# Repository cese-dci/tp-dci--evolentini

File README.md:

# Punku, Control de Accesos

## Diagramas de Hardware

Este repositorio contiene el los diagramas esquematicos y diseño de placas del equipo apra control de accesos Punku. Los mismo estan realizados utilizando la el programa [KiCad](http://kicad.org/)

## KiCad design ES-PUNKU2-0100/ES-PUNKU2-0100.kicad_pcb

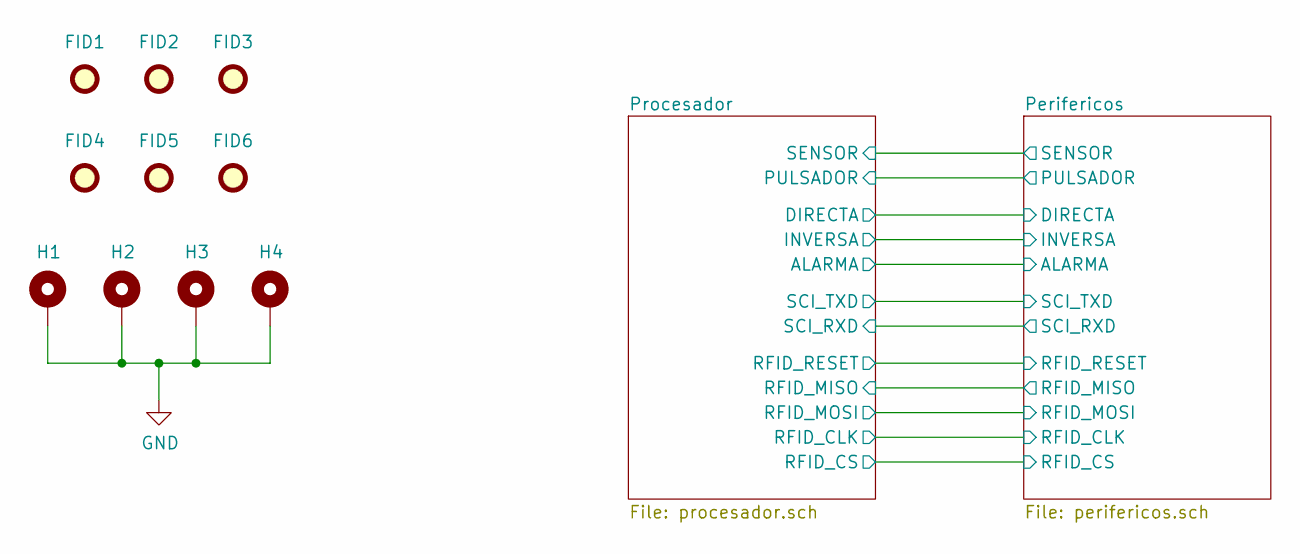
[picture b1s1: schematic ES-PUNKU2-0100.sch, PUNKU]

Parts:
FID1, FID2, FID3, FID4, FID5, FID6: Fiducial; Fiducial_0.5mm_Mask1mm
H1, H2, H3, H4: MountingHole_Pad; MountingHole_4mm_Pad

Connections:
GND: H1.1, H2.1, H3.1, H4.1; also elsewhere on the board

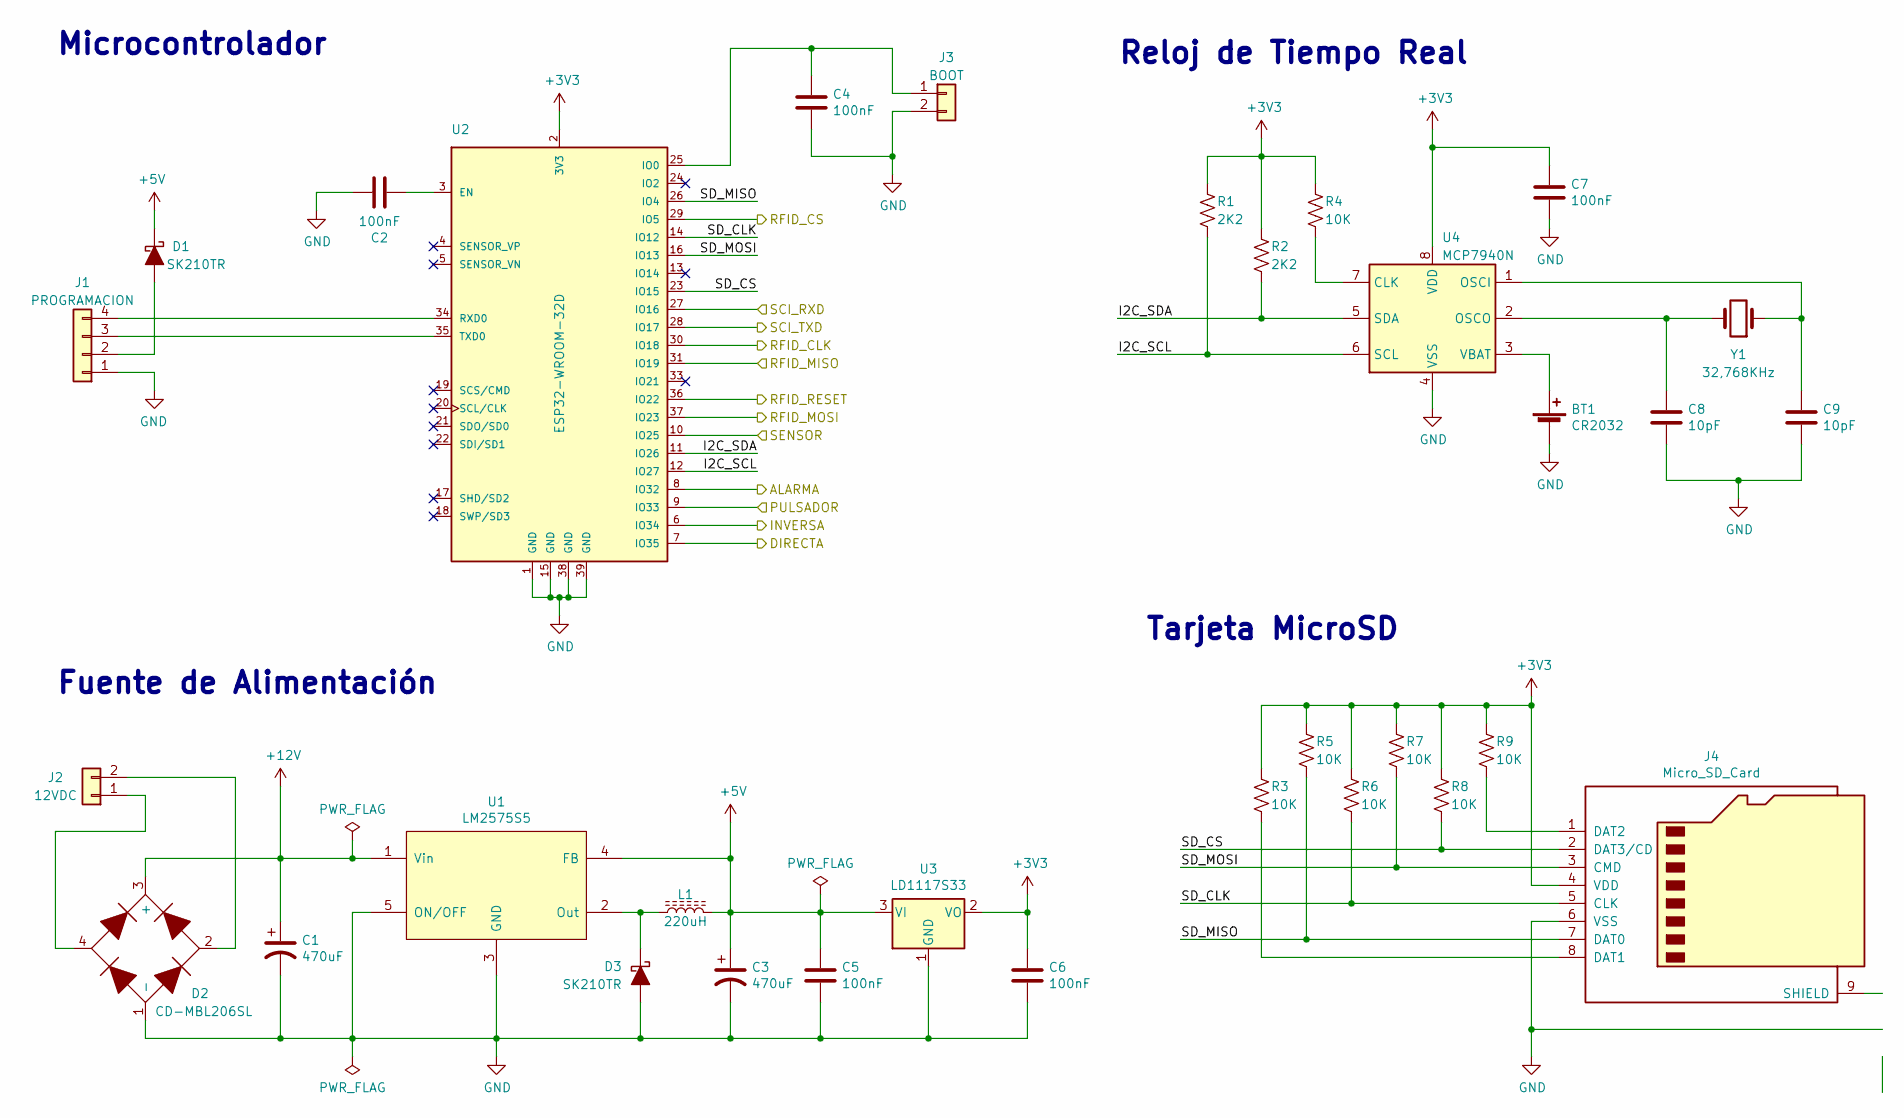
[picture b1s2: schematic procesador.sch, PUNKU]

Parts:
BT1: CR2032; BatteryHolder_Keystone_1058_1x2032; DigiKey 36-1058-ND
C1, C3: 470uF; CP_Elec_8x10
C2, C4, C5, C6, C7: 100nF; C_1206_0805_Dual
C8, C9: 10pF; C_1206_0805_Dual
D1, D3: SK210TR; DO-214AA; DigiKey 1655-1584-1-ND
D2: CD-MBL206SL; BOURNS-0.23x0.20; DigiKey CD-MBL206SLCT-ND
J1: PROGRAMACION; Pin_Header_Straight_1x04_Pitch2.54mm
J2: 12VDC; Bornera_Recta_2_0.200_Inch
J3: BOOT; Pin_Header_Straight_1x02_Pitch2.54mm
J4: Micro_SD_Card; SD_AMPHENOL_114_00841_68; DigiKey 114-00841-68-1-ND
L1: 220uH; BOURNS_INDUCTOR_SRR1260; DigiKey SRR1280-331KLCT-ND
R1, R2: 2K2; R_1206_0805_Dual
R3, R4, R5, R6, R7, R8, R9: 10K; R_1206_0805_Dual
U1: LM2575S5; D2PAK_TO-263_5Patas; DigiKey LM2575S-5.0/NOPB-ND
U2: ESP32-WROOM-32D; MODULE_ESP32-WROOM-32D; DigiKey 1904-1023-1-ND
U3: LD1117S33; SOT-223-3_TabPin2; DigiKey 497-1241-1-ND
U4: MCP7940N; SOIC-8; DigiKey MCP7940NT-I/SNCT-ND
Y1: 32,768KHz; CRISTAL_EPSON_3,2mm_1,5mm; DigiKey SER4089CT-ND

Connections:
+3V3: C6.1, C7.1, J4.4 (VDD), R1.1, R2.1, R3.1, R4.1, R5.1, R6.1, R7.1, R8.1, R9.1, U2.2 (3V3), U3.2 (VO), U4.8 (VDD); also elsewhere on the board
+5V: C3.1, C5.1, D1.1 (K), L1.2, U1.4 (FB), U3.3 (VI); also elsewhere on the board
+12V: C1.1, D2.3 (+), U1.1 (Vin); also elsewhere on the board
/Perifericos/ALARMA: U2.8 (IO32); also elsewhere on the board
/Perifericos/DIRECTA: U2.7 (IO35); also elsewhere on the board
/Perifericos/INVERSA: U2.6 (IO34); also elsewhere on the board
/Perifericos/PULSADOR: U2.9 (IO33); also elsewhere on the board
/Perifericos/RFID_CLK: U2.30 (IO18); also elsewhere on the board
/Perifericos/RFID_CS: U2.29 (IO5); also elsewhere on the board
/Perifericos/RFID_MISO: U2.31 (IO19); also elsewhere on the board
/Perifericos/RFID_MOSI: U2.37 (IO23); also elsewhere on the board
/Perifericos/RFID_RESET: U2.36 (IO22); also elsewhere on the board
/Perifericos/SCI_RXD: U2.27 (IO16); also elsewhere on the board
/Perifericos/SCI_TXD: U2.28 (IO17); also elsewhere on the board
/Perifericos/SENSOR: U2.10 (IO25); also elsewhere on the board
/Procesador/I2C_SCL: R1.2, U2.12 (IO27), U4.6 (SCL)
/Procesador/I2C_SDA: R2.2, U2.11 (IO26), U4.5 (SDA)
/Procesador/SD_CLK: J4.5 (CLK), R6.2, U2.14 (IO12)
/Procesador/SD_CS: J4.2 (DAT3/CD), R8.2, U2.23 (IO15)
/Procesador/SD_MISO: J4.7 (DAT0), R5.2, U2.26 (IO4)
/Procesador/SD_MOSI: J4.3 (CMD), R7.2, U2.16 (IO13)
GND: BT1.2 (-), C1.2, C2.1, C3.2, C4.1, C5.2, C6.2, C7.2, C8.2, C9.2, D2.1 (-), D3.2 (A), J1.1, J3.2, J4.6 (VSS), J4.9 (SHIELD), U1.3 (GND), U1.5 (ON/OFF), U2.1 (GND), U2.15 (GND), U2.38 (GND), U2.39 (GND), U3.1 (GND), U4.4 (VSS); also elsewhere on the board
unnamed: BT1.1 (+), U4.3 (VBAT)
unnamed: C2.2, U2.3 (EN)
unnamed: C4.2, J3.1, U2.25 (IO0)
unnamed: C8.1, U4.2 (OSCO), Y1.2
unnamed: C9.1, U4.1 (OSCI), Y1.1
unnamed: D1.2 (A), J1.2
unnamed: D2.2, J2.2
unnamed: D2.4, J2.1
unnamed: D3.1 (K), L1.1, U1.2 (Out)
unnamed: J1.3, U2.35 (TXD0)
unnamed: J1.4, U2.34 (RXD0)
unnamed: J4.1 (DAT2), R9.2
unnamed: J4.8 (DAT1), R3.2
unnamed: R4.2, U4.7 (CLK)

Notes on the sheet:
Microcontrolador
Tarjeta MicroSD
Reloj de Tiempo Real
Fuente de Alimentación

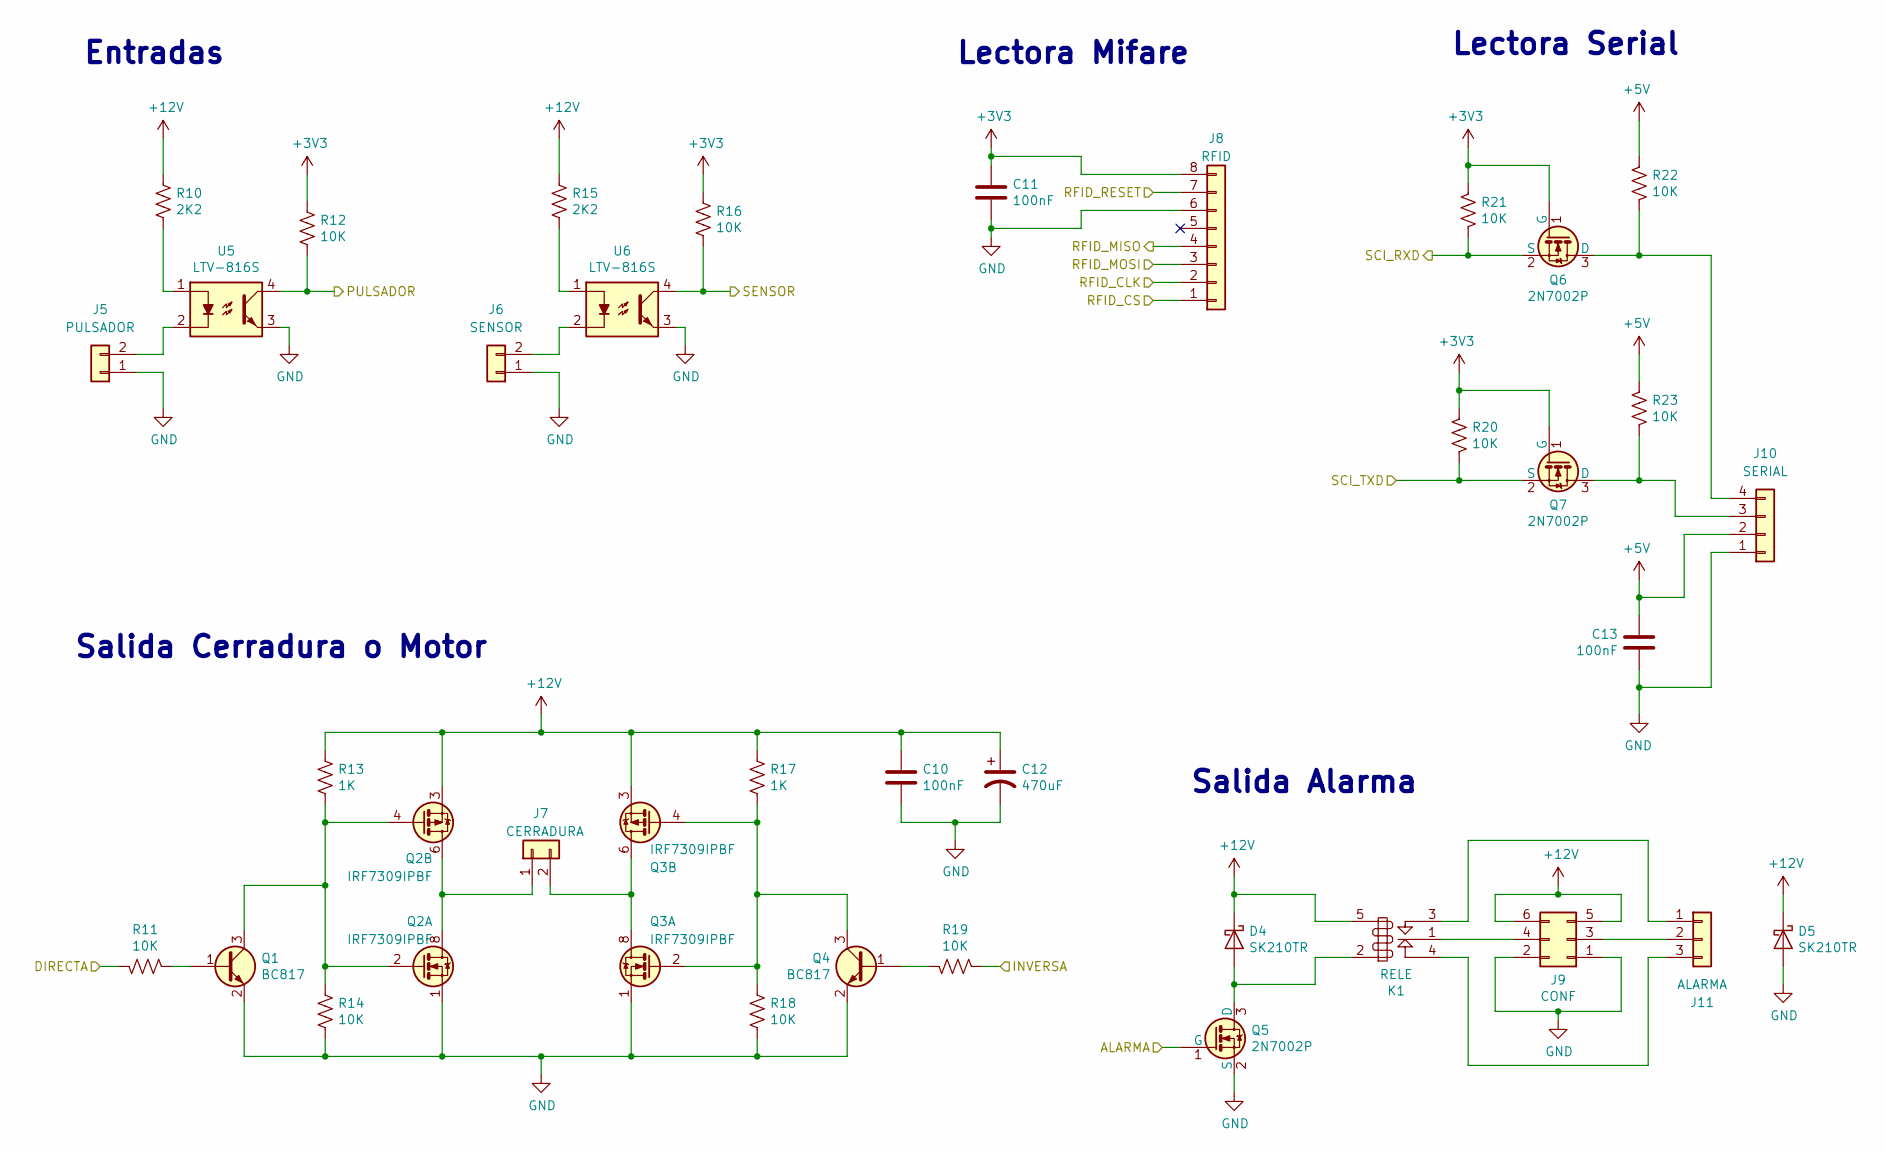
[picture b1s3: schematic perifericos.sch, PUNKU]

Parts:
C10, C11, C13: 100nF; C_1206_0805_Dual
C12: 470uF; CP_Elec_8x10
D4, D5: SK210TR; DO-214AA; DigiKey 1655-1584-1-ND
J5: PULSADOR; Bornera_Angulo_2_0.150_Inch
J6: SENSOR; Bornera_Angulo_2_0.150_Inch
J7: CERRADURA; Bornera_Angulo_2_0.150_Inch
J8: RFID; PinHeader_2x04_P2.54mm_Vertical_SMD
J9: CONF; Pin_Header_Straight_2x03_Pitch2.54mm
J10: SERIAL; Pin_Header_Straight_1x04_Pitch2.54mm
J11: ALARMA; Bornera_Angulo_3_0.150_Inch
K1: RELE; Relay_NT78_Series_Form_C
Q1, Q4: BC817; SOT-23; DigiKey 1727-1978-1-ND
Q2, Q3: IRF7309IPBF; SOIC-8; DigiKey IRF7309PBFCT-ND
Q5, Q6, Q7: 2N7002P; SOT-23; DigiKey 1727-4692-1-ND
R10, R15: 2K2; R_1206_0805_Dual
R11, R12, R14, R16, R18, R19, R20, R21, R22, R23: 10K; R_1206_0805_Dual
R13, R17: 1K; R_1206_0805_Dual
U5, U6: LTV-816S; DIL-8-SMD; DigiKey 160-1361-5-ND

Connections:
+3V3: C11.1, J8.8, Q6.1 (G), Q7.1 (G), R12.1, R16.1, R20.1, R21.1; also elsewhere on the board
+5V: C13.1, J10.2, R22.1, R23.1; also elsewhere on the board
+12V: C10.1, C12.1, D4.1 (K), D5.1 (K), J9.5, J9.6, K1.5 (B2), Q2.3 (1), Q3.3 (1), R10.1, R13.1, R15.1, R17.1; also elsewhere on the board
/Perifericos/ALARMA: Q5.1 (G); also elsewhere on the board
/Perifericos/DIRECTA: R11.2; also elsewhere on the board
/Perifericos/INVERSA: R19.1; also elsewhere on the board
/Perifericos/PULSADOR: R12.2, U5.4; also elsewhere on the board
/Perifericos/RFID_CLK: J8.2; also elsewhere on the board
/Perifericos/RFID_CS: J8.1; also elsewhere on the board
/Perifericos/RFID_MISO: J8.4; also elsewhere on the board
/Perifericos/RFID_MOSI: J8.3; also elsewhere on the board
/Perifericos/RFID_RESET: J8.7; also elsewhere on the board
/Perifericos/SCI_RXD: Q6.2 (S), R21.2; also elsewhere on the board
/Perifericos/SCI_TXD: Q7.2 (S), R20.2; also elsewhere on the board
/Perifericos/SENSOR: R16.2, U6.4; also elsewhere on the board
GND: C10.2, C11.2, C12.2, C13.2, D5.2 (A), J5.1, J6.1, J8.6, J9.1, J9.2, J10.1, Q1.2 (E), Q2.1 (S), Q3.1 (S), Q4.2 (E), Q5.2 (S), R14.2, R18.2, U5.3, U6.3; also elsewhere on the board
unnamed: D4.2 (A), K1.2 (B1), Q5.3 (D)
unnamed: J5.2, U5.2
unnamed: J6.2, U6.2
unnamed: J7.1, Q2.5 (D), Q2.6 (D), Q2.7 (D), Q2.8 (D)
unnamed: J9.4, K1.1 (C)
unnamed: J10.3, Q7.3 (D), R23.2
unnamed: J10.4, Q6.3 (D), R22.2
unnamed: J11.1, K1.3 (NA)
unnamed: J9.3, J11.2
unnamed: J11.3, K1.4 (NC)
unnamed: Q1.1 (B), R11.1
unnamed: Q1.3 (C), Q2.2 (G), Q2.4 (G), R13.2, R14.1
unnamed: Q3.2 (G), Q3.4 (G), Q4.3 (C), R17.2, R18.1
unnamed: Q4.1 (B), R19.2
unnamed: R10.2, U5.1
unnamed: R15.2, U6.1

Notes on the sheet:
Entradas
Salida Cerradura o Motor
Salida Alarma
Lectora Mifare
Lectora Serial

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
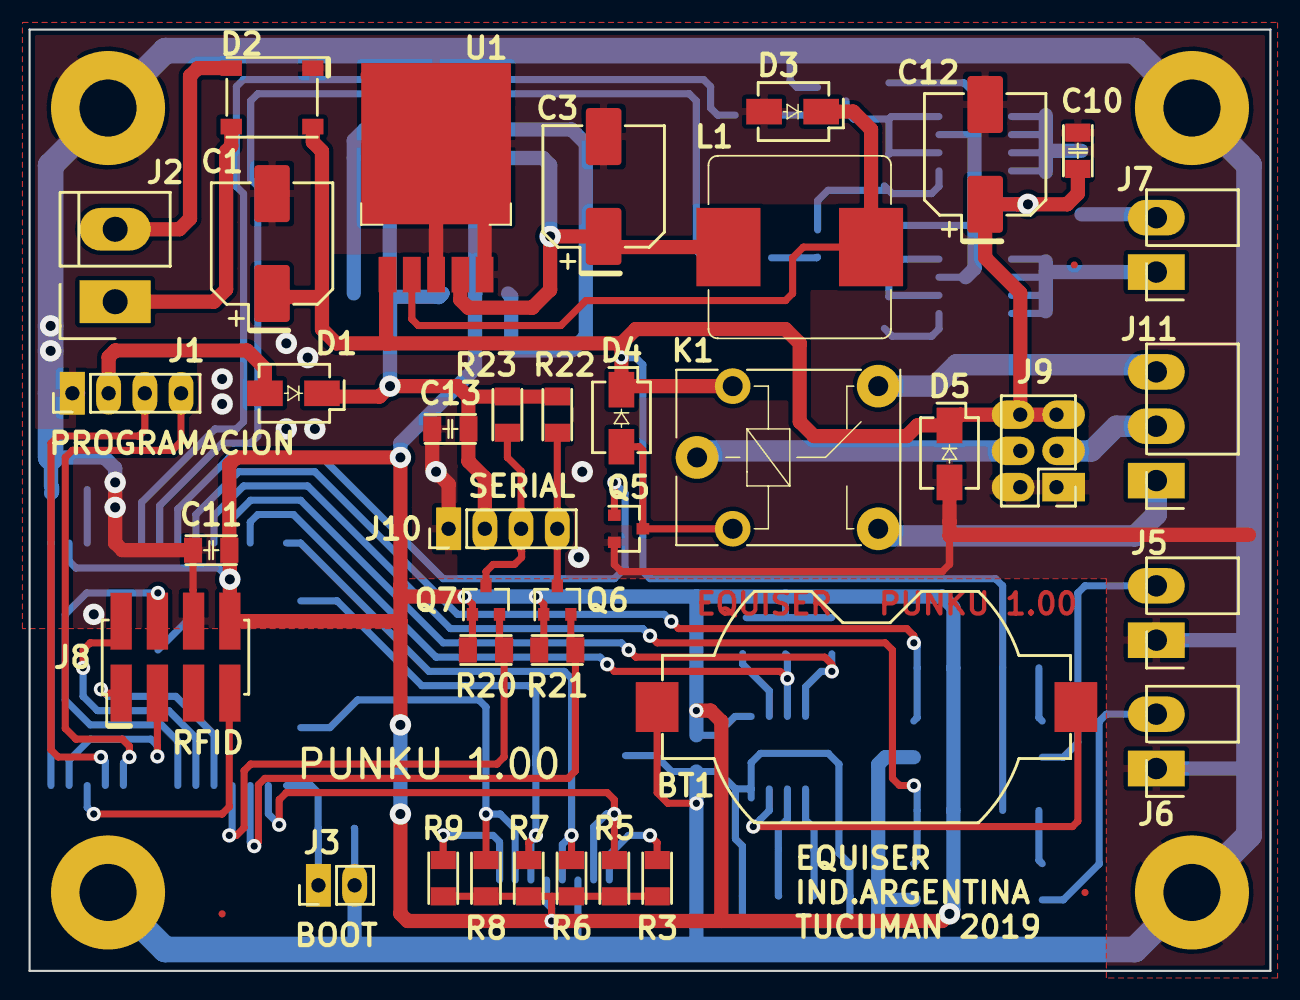
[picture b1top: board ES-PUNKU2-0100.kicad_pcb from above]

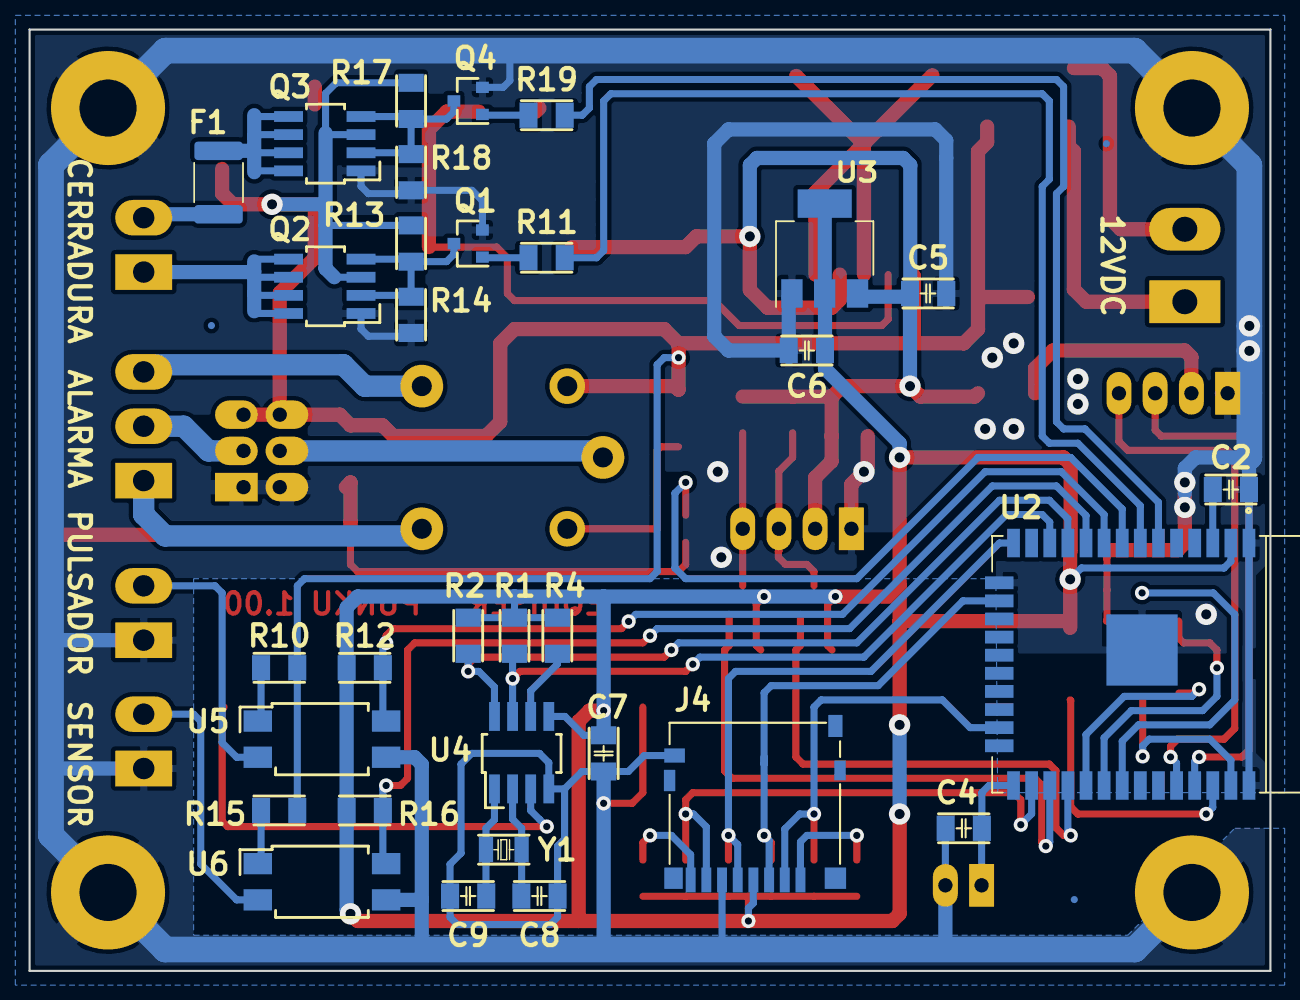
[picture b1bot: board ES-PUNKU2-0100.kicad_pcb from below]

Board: 2 copper layers, 87.0 x 66.0 mm, 80 parts (35 on the bottom side), 54 nets.

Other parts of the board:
F1: Polyfuse; R_1812_4532Metric_Pad1.30x3.40mm_HandSolder

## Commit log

2019-09-12 Version inicial del diagrama esquemático y de la librería propia
2019-09-23 Correcciones al esquemático. Asignación de referencias y valores. Actualización de Librerías.
2019-10-04 Incorporación de las correcciones sugeridas por Martin Ribelotta y posicionamiento de componentes
2019-10-15 Primera versión ruteada de la placa
2019-10-15 Correcciónes y exportacion del modelo 3D de la placa
2019-10-18 Correcciones de ruteo y agregado de una protección para la salida del puente H
2019-11-07 Correcciones finales
2021-11-09 Update README.md
    https://forum.kicad.info/t/warning-avoid-all-links-to-kicad-pcb-org-use-kicad-org/31521
